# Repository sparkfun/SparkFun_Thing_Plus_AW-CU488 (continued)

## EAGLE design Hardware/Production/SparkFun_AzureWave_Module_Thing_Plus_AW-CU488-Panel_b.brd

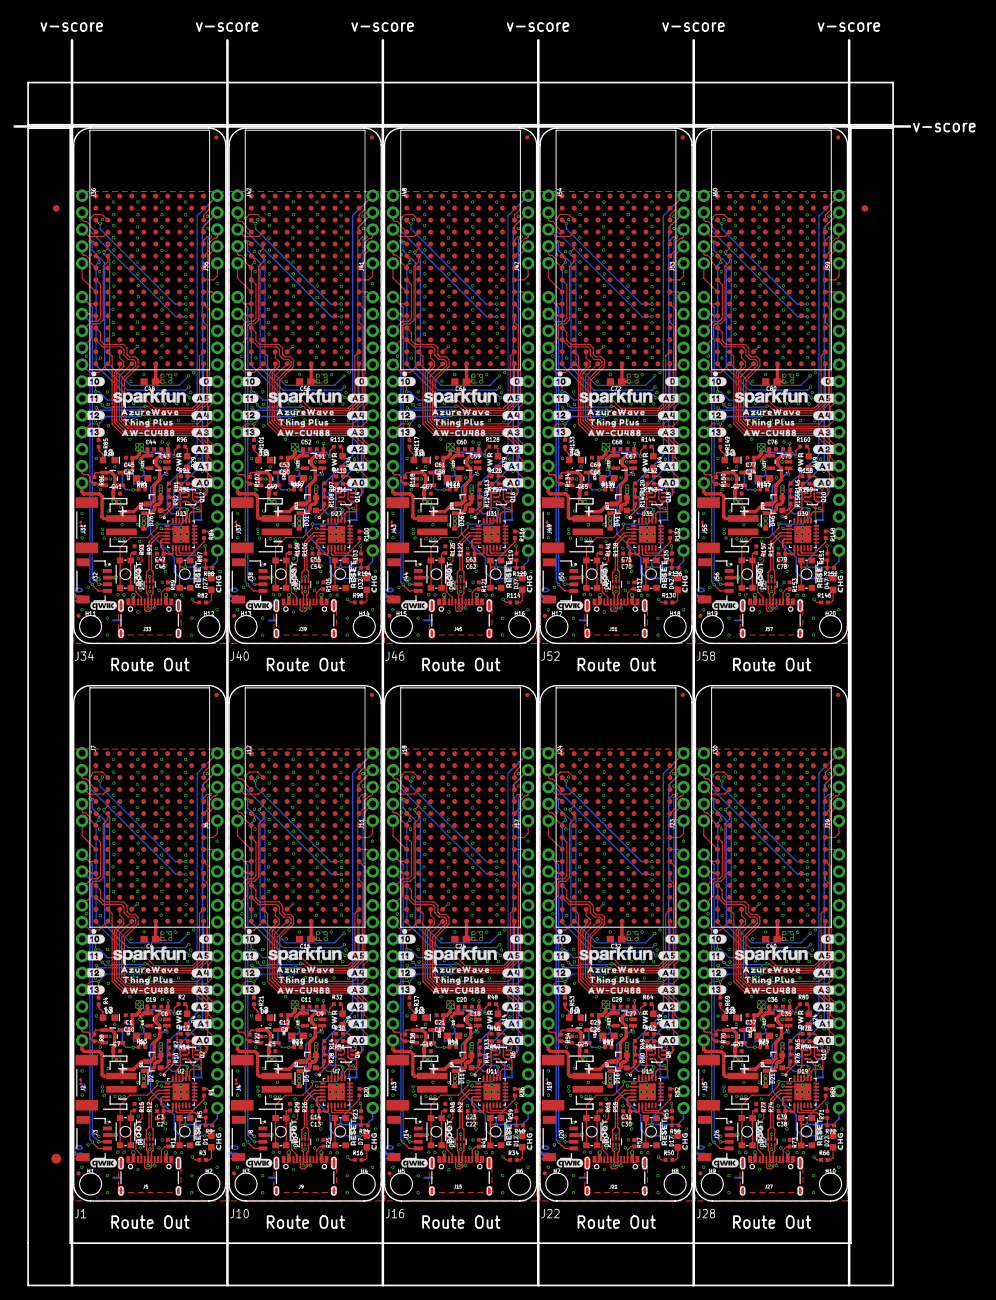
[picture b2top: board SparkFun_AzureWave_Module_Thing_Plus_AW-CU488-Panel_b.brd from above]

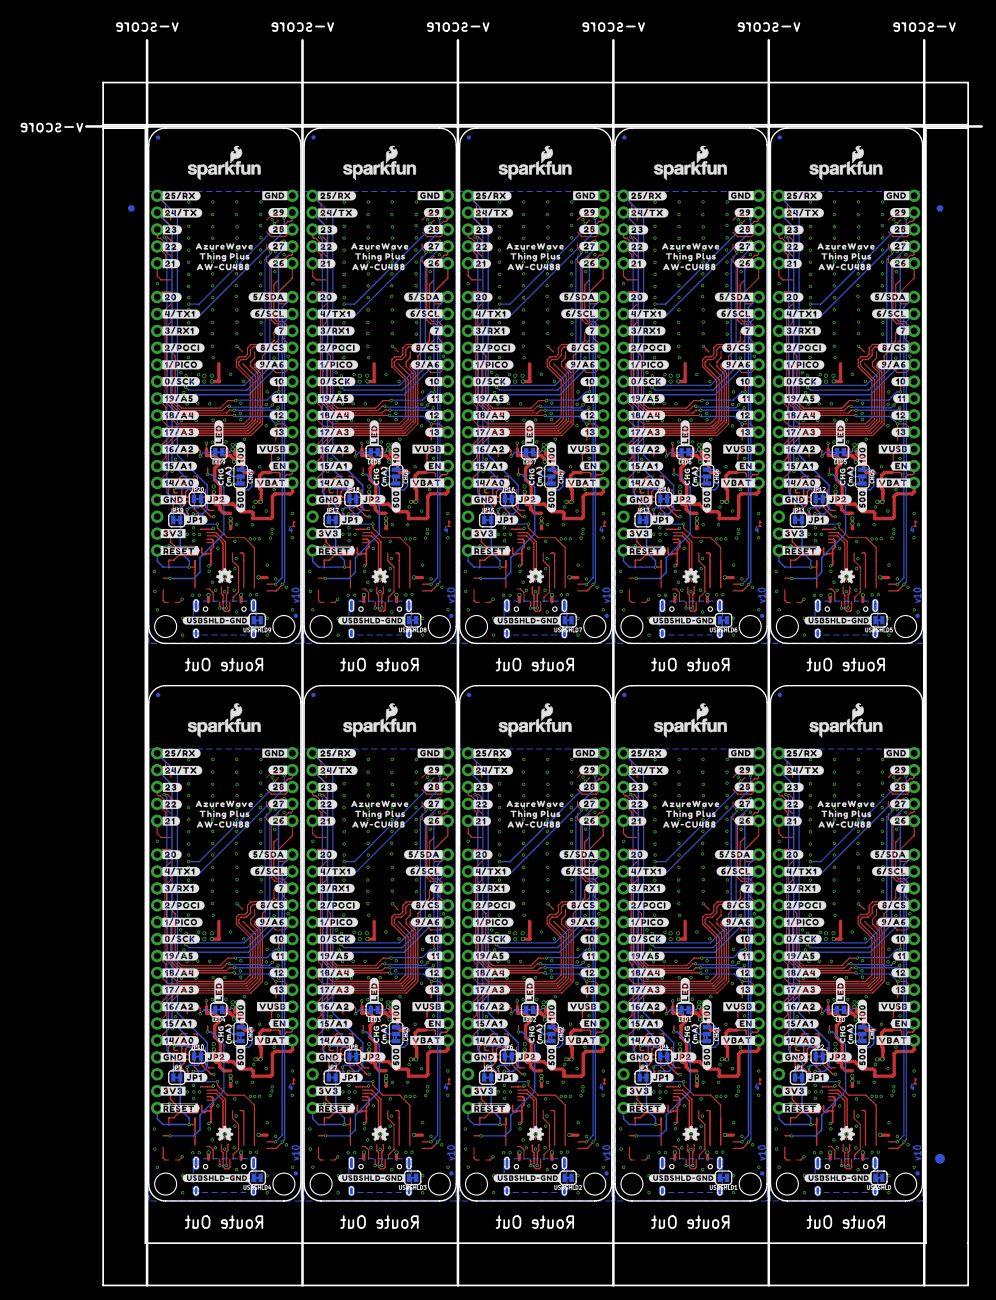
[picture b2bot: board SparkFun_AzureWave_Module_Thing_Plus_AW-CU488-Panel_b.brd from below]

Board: 4 copper layers, 134.6 x 187.2 mm, 1276 parts (573 on the bottom side), 620 nets.

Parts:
C1, C12, C21, C29, C37, C45, C53, C61, C69, C77: 10uF; 0402-TIGHT
C2, C13, C22, C30, C38, C46, C54, C62, C70, C78: 0.1uF; 0402-TIGHT
C3, C6, C9, C11, C14, C18, C19, C20, C23, C27, C28, C31, C35, C36, C39, C43, C44, C47, C51, C52, C55, C59, C60, C63, C67, C68, C71, C75, C76, C79: 4.7uF; 0402-TIGHT
C4, C15, C24, C32, C40, C48, C56, C64, C72, C80: 10uF; 0603
C5, C7, C8, C10, C16, C17, C25, C26, C33, C34, C41, C42, C49, C50, C57, C58, C65, C66, C73, C74: 1.0uF; 0402-TIGHT
CHG, CHG1, CHG2, CHG3, CHG4, CHG5, CHG6, CHG7, CHG8, CHG9: SMT-JUMPER_3_1-NC_TRACE_SILK
D1, D7, D12, D17, D22, D27, D32, D37, D42, D47: Yellow; LED-0603
D2, D5, D11, D16, D21, D26, D31, D36, D41, D46: 1A/23V/620mV; SOD-323
D3, D8, D13, D18, D23, D28, D33, D38, D43, D48: BLUE; LED-0603
D4, D9, D14, D19, D24, D29, D34, D39, D44, D49: RED; LED-0603
D6, D10, D15, D20, D25, D30, D35, D40, D45, D50: PRTR5V0U2F; SOT886
E$1, E$2, E$3, E$4: FIDUCIAL-1X2
E$5, E$6: FIDUCIAL-1.5X3
FD1, FD2, FD3, FD4, FD5, FD6, FD7, FD8, FD9, FD10, FD11, FD12, FD13, FD14, FD15, FD16, FD17, FD18, FD19, FD20, FD21, FD22, FD23, FD24, FD25, FD26, FD27, FD28, FD29, FD30, FD31, FD32, FD33, FD34, FD35, FD36, FD37, FD38, FD39, FD40: FIDUCIALUFIDUCIAL; FIDUCIAL-MICRO
H1, H2, H3, H4, H5, H6, H7, H8, H9, H10, H11, H12, H13, H14, H15, H16, H17, H18, H19, H20: STAND-OFF
J1, J10, J16, J22, J28, J34, J40, J46, J52, J58: THING_PLUS
J2, J4, J13, J19, J25, J31, J37, J43, J49, J55: LiPo; JST-2-SMD
J3, J8, J14, J20, J26, J32, J38, J44, J50, J56: QWIIC_RA; JST04_1MM_RA
J5, J9, J15, J21, J27, J33, J39, J45, J51, J57: USB-C; USB-C-16P-4LAYER-ISOLATED
J6, J7, J11, J12, J17, J18, J23, J24, J29, J30, J35, J36, J41, J42, J47, J48, J53, J54, J59, J60: 1X05_NO_SILK
JP1, JP2, JP3, JP4, JP5, JP6, JP7, JP8, JP9, JP10, JP11, JP12, JP13, JP14, JP15, JP16, JP17, JP18, JP19, JP20: SMT-JUMPER_2_NC_TRACE_SILK
LED, LED1, LED2, LED3, LED4, LED5, LED6, LED7, LED8, LED9: SMT-JUMPER_2_NC_TRACE_SILK
LOGO1, LOGO9, LOGO14, LOGO19, LOGO24, LOGO29, LOGO34, LOGO39, LOGO44, LOGO49: SFE_LOGO_NAME.1_INCH; SFE_LOGO_NAME_.1
LOGO2, LOGO5, LOGO11, LOGO16, LOGO21, LOGO26, LOGO31, LOGO36, LOGO41, LOGO46: OSHW-LOGOMINI; OSHW-LOGO-MINI
LOGO3, LOGO10, LOGO15, LOGO20, LOGO25, LOGO30, LOGO35, LOGO40, LOGO45, LOGO50: SFE_LOGO_NAME_FLAME.1_INCH; SFE_LOGO_NAME_FLAME_.1
LOGO4, LOGO7, LOGO12, LOGO17, LOGO22, LOGO27, LOGO32, LOGO37, LOGO42, LOGO47: FOUR_LAYER_WARNING
LOGO6, LOGO8, LOGO13, LOGO18, LOGO23, LOGO28, LOGO33, LOGO38, LOGO43, LOGO48: QWIIC_LOGO_4MM; QWIIC_4MM
Q1, Q3, Q5, Q7, Q9, Q11, Q13, Q15, Q17, Q19: 3.1A/30V/105mΩ; SOT23-3
Q2, Q4, Q6, Q8, Q10, Q12, Q14, Q16, Q18, Q20: MBT3904DW1T1; SC70-6
R1, R7, R13, R14, R17, R18, R20, R27, R30, R31, R33, R36, R43, R46, R47, R49, R52, R59, R62, R63, R65, R68, R75, R78, R79, R81, R84, R91, R94, R95, R97, R100, R107, R110, R111, R113, R116, R123, R126, R127, R129, R132, R139, R142, R143, R145, R148, R155, R158, R159: 10k; 0402-TIGHT
R2, R15, R29, R32, R45, R48, R61, R64, R77, R80, R93, R96, R109, R112, R125, R128, R141, R144, R157, R160: 1k; 0402-TIGHT
R3, R4, R16, R21, R34, R37, R50, R53, R66, R69, R82, R85, R98, R101, R114, R117, R130, R133, R146, R149: 4.7k; 0402-TIGHT
R5, R23, R39, R55, R71, R87, R103, R119, R135, R151: 22k; 0402-TIGHT
R6, R19, R35, R51, R67, R83, R99, R115, R131, R147: 2.0k; 0603
R8, R22, R38, R54, R70, R86, R102, R118, R134, R150: 100k; 0402-TIGHT
R9, R24, R40, R56, R72, R88, R104, R120, R136, R152: 33k; 0402-TIGHT
R10, R28, R44, R60, R76, R92, R108, R124, R140, R156: 100; 0402-TIGHT
R11, R12, R25, R26, R41, R42, R57, R58, R73, R74, R89, R90, R105, R106, R121, R122, R137, R138, R153, R154: 5.1k; 0402-TIGHT
S1, S3, S5, S7, S9, S11, S13, S15, S17, S19: SW1/RESET; TACTILE_SWITCH_SMD_4.6X2.8MM
S2, S4, S6, S8, S10, S12, S14, S16, S18, S20: SW2/BOOT; TACTILE_SWITCH_SMD_4.6X2.8MM
U1, U8, U12, U16, U20, U24, U28, U32, U36, U40: AW-CU488; LGA150_AW-CU488
U2, U7, U11, U15, U19, U23, U27, U31, U35, U39: CP210X; QFN24
U3, U6, U10, U14, U18, U22, U26, U30, U34, U38: XC6222B331MR-G; SOT23-5
U4, U5, U9, U13, U17, U21, U25, U29, U33, U37: MCP73831; SOT23-5
U$1, U$129, U$197, U$265, U$333, U$401, U$469, U$537, U$605, U$673: #10#30
U$2, U$38, U$152, U$220, U$288, U$356, U$424, U$492, U$560, U$628: BOOT0
U$3, U$17, U$31, U$78, U$138, U$146, U$206, U$214, U$274, U$282, U$342, U$350, U$410, U$418, U$478, U$486, U$546, U$554, U$614, U$622: CHG0
U$4, U$35, U$149, U$217, U$285, U$353, U$421, U$489, U$557, U$625: #500#0
U$5, U$130, U$198, U$266, U$334, U$402, U$470, U$538, U$606, U$674: #11#30
U$6, U$8, U$39, U$40, U$153, U$154, U$221, U$222, U$289, U$290, U$357, U$358, U$425, U$426, U$493, U$494, U$561, U$562, U$629, U$630: AZUREWAVE0
U$7, U$133, U$201, U$269, U$337, U$405, U$473, U$541, U$609, U$677: 1330
U$9, U$27, U$37, U$44, U$151, U$155, U$219, U$223, U$287, U$291, U$355, U$359, U$423, U$427, U$491, U$495, U$559, U$563, U$627, U$631: AW#CU488_0
U$10, U$36, U$47, U$62, U$150, U$156, U$218, U$224, U$286, U$292, U$354, U$360, U$422, U$428, U$490, U$496, U$558, U$564, U$626, U$632: THING_PLUS_0
U$11, U$33, U$147, U$215, U$283, U$351, U$419, U$487, U$555, U$623: MA0
U$12, U$131, U$199, U$267, U$335, U$403, U$471, U$539, U$607, U$675: #12#30
U$13, U$59, U$137, U$205, U$273, U$341, U$409, U$477, U$545, U$613: ORDERING_INSTRUCTIONS
U$14, U$132, U$200, U$268, U$336, U$404, U$472, U$540, U$608, U$676: #13#30
U$15, U$135, U$203, U$271, U$339, U$407, U$475, U$543, U$611, U$679: #JP1#1
U$16, U$134, U$202, U$270, U$338, U$406, U$474, U$542, U$610, U$678: #0#1
U$18, U$65, U$162, U$230, U$298, U$366, U$434, U$502, U$570, U$638: #A0#30
U$19, U$136, U$204, U$272, U$340, U$408, U$476, U$544, U$612, U$680: #JP2#4
U$20, U$66, U$163, U$231, U$299, U$367, U$435, U$503, U$571, U$639: #USBSHLD#GND#3
U$21, U$79, U$139, U$207, U$275, U$343, U$411, U$479, U$547, U$615: RESET0
U$22, U$41, U$140, U$208, U$276, U$344, U$412, U$480, U$548, U$616: #VUSB#0
U$23, U$96, U$164, U$232, U$300, U$368, U$436, U$504, U$572, U$640: PWR0
U$24, U$42, U$141, U$209, U$277, U$345, U$413, U$481, U$549, U$617: #VBAT#0
U$25, U$43, U$142, U$210, U$278, U$346, U$414, U$482, U$550, U$618: #EN#0
U$26, U$32, U$86, U$119, U$143, U$187, U$211, U$255, U$279, U$323, U$347, U$391, U$415, U$459, U$483, U$527, U$551, U$595, U$619, U$663: #GND#0
U$28, U$45, U$144, U$212, U$280, U$348, U$416, U$484, U$552, U$620: #3V3#0
U$29, U$97, U$165, U$233, U$301, U$369, U$437, U$505, U$573, U$641: #LED#0
U$30, U$46, U$145, U$213, U$281, U$349, U$417, U$485, U$553, U$621: ##RESET##0
U$34, U$60, U$148, U$216, U$284, U$352, U$420, U$488, U$556, U$624: #100#0
U$48, U$107, U$175, U$243, U$311, U$379, U$447, U$515, U$583, U$651: #4#TX1#14
U$49, U$108, U$176, U$244, U$312, U$380, U$448, U$516, U$584, U$652: #3#RX1#14
U$50, U$109, U$177, U$245, U$313, U$381, U$449, U$517, U$585, U$653: #2#POCI#14
U$51, U$53, U$157, U$225, U$293, U$361, U$429, U$497, U$565, U$633: #A1#6
U$52, U$54, U$158, U$226, U$294, U$362, U$430, U$498, U$566, U$634: #A2#6
U$55, U$58, U$159, U$227, U$295, U$363, U$431, U$499, U$567, U$635: #A3#6
U$56, U$61, U$160, U$228, U$296, U$364, U$432, U$500, U$568, U$636: #A4#6
U$57, U$63, U$161, U$229, U$297, U$365, U$433, U$501, U$569, U$637: #A5#6
U$64, U$110, U$178, U$246, U$314, U$382, U$450, U$518, U$586, U$654: #1#PICO#14
U$67, U$98, U$166, U$234, U$302, U$370, U$438, U$506, U$574, U$642: #13#14
U$68, U$99, U$167, U$235, U$303, U$371, U$439, U$507, U$575, U$643: #12#14
U$69, U$100, U$168, U$236, U$304, U$372, U$440, U$508, U$576, U$644: #11#14
U$70, U$101, U$169, U$237, U$305, U$373, U$441, U$509, U$577, U$645: #10#14
U$71, U$102, U$170, U$238, U$306, U$374, U$442, U$510, U$578, U$646: #9#A6#14
U$72, U$103, U$171, U$239, U$307, U$375, U$443, U$511, U$579, U$647: #8#CS#14
U$73, U$104, U$172, U$240, U$308, U$376, U$444, U$512, U$580, U$648: #7#14
U$74, U$105, U$173, U$241, U$309, U$377, U$445, U$513, U$581, U$649: #6#SCL#14
U$75, U$106, U$174, U$242, U$310, U$378, U$446, U$514, U$582, U$650: #5#SDA#14
U$76, U$111, U$179, U$247, U$315, U$383, U$451, U$519, U$587, U$655: #0#SCK#14
U$77, U$112, U$180, U$248, U$316, U$384, U$452, U$520, U$588, U$656: #14#A0#15
U$80, U$113, U$181, U$249, U$317, U$385, U$453, U$521, U$589, U$657: #15#A1#15
U$81, U$114, U$182, U$250, U$318, U$386, U$454, U$522, U$590, U$658: #16#A2#16
U$82, U$115, U$183, U$251, U$319, U$387, U$455, U$523, U$591, U$659: #17#A3#17
U$83, U$116, U$184, U$252, U$320, U$388, U$456, U$524, U$592, U$660: #18#A4#18
U$84, U$117, U$185, U$253, U$321, U$389, U$457, U$525, U$593, U$661: #19#A5#19
U$85, U$118, U$186, U$254, U$322, U$390, U$458, U$526, U$594, U$662: #20#20
U$87, U$120, U$188, U$256, U$324, U$392, U$460, U$528, U$596, U$664: #21#21
U$88, U$121, U$189, U$257, U$325, U$393, U$461, U$529, U$597, U$665: #22#22
U$89, U$122, U$190, U$258, U$326, U$394, U$462, U$530, U$598, U$666: #23#23
U$90, U$123, U$191, U$259, U$327, U$395, U$463, U$531, U$599, U$667: #24#TX#24
U$91, U$124, U$192, U$260, U$328, U$396, U$464, U$532, U$600, U$668: #25#RX#25
U$92, U$125, U$193, U$261, U$329, U$397, U$465, U$533, U$601, U$669: #26#26
U$93, U$126, U$194, U$262, U$330, U$398, U$466, U$534, U$602, U$670: #27#27
U$94, U$127, U$195, U$263, U$331, U$399, U$467, U$535, U$603, U$671: #28#28
U$95, U$128, U$196, U$264, U$332, U$400, U$468, U$536, U$604, U$672: #29#29
USBSHLD, USBSHLD1, USBSHLD2, USBSHLD3, USBSHLD4, USBSHLD5, USBSHLD6, USBSHLD7, USBSHLD8, USBSHLD9: SMT-JUMPER_2_NC_TRACE_SILK

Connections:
3.3V: C1.1, C2.1, C3.1, C4.1, C10.1, J1.27, J3.2, LED.1, R1.1, U1.F1, U2.5, U2.6, U2.7, U3.5
3.3V1: C8.1, C12.1, C13.1, C14.1, C15.1, J8.2, J10.27, LED1.1, R20.1, U6.5, U7.5, U7.6, U7.7, U8.F1
3.3V2: C17.1, C21.1, C22.1, C23.1, C24.1, J14.2, J16.27, LED2.1, R36.1, U10.5, U11.5, U11.6, U11.7, U12.F1
3.3V3: C26.1, C29.1, C30.1, C31.1, C32.1, J20.2, J22.27, LED3.1, R52.1, U14.5, U15.5, U15.6, U15.7, U16.F1
3.3V4: C34.1, C37.1, C38.1, C39.1, C40.1, J26.2, J28.27, LED4.1, R68.1, U18.5, U19.5, U19.6, U19.7, U20.F1
3.3V5: C42.1, C45.1, C46.1, C47.1, C48.1, J32.2, J34.27, LED5.1, R84.1, U22.5, U23.5, U23.6, U23.7, U24.F1
3.3V6: C50.1, C53.1, C54.1, C55.1, C56.1, J38.2, J40.27, LED6.1, R100.1, U26.5, U27.5, U27.6, U27.7, U28.F1
3.3V7: C58.1, C61.1, C62.1, C63.1, C64.1, J44.2, J46.27, LED7.1, R116.1, U30.5, U31.5, U31.6, U31.7, U32.F1
3.3V8: C66.1, C69.1, C70.1, C71.1, C72.1, J50.2, J52.27, LED8.1, R132.1, U34.5, U35.5, U35.6, U35.7, U36.F1
3.3V9: C74.1, C77.1, C78.1, C79.1, C80.1, J56.2, J58.27, LED9.1, R148.1, U38.5, U39.5, U39.6, U39.7, U40.F1
CC1: J5.A5, R12.2
CC2: J5.B5, R11.2
CC3: J9.B5, R25.2
CC4: J9.A5, R26.2
CC5: J15.B5, R41.2
CC6: J15.A5, R42.2
CC7: J21.B5, R57.2
CC8: J21.A5, R58.2
CC9: J27.B5, R73.2
CC10: J27.A5, R74.2
CC11: J33.B5, R89.2
CC12: J33.A5, R90.2
CC13: J39.B5, R105.2
CC14: J39.A5, R106.2
CC15: J45.B5, R121.2
CC16: J45.A5, R122.2
CC17: J51.B5, R137.2
CC18: J51.A5, R138.2
CC19: J57.B5, R153.2
CC20: J57.A5, R154.2
CHG: D1.C, U4.1
CHG1: D7.C, U5.1
CHG2: D12.C, U9.1
CHG3: D17.C, U13.1
CHG4: D22.C, U17.1
CHG5: D27.C, U21.1
CHG6: D32.C, U25.1
CHG7: D37.C, U29.1
CHG8: D42.C, U33.1
CHG9: D47.C, U37.1
CHIP_EN: J1.28, JP1.2, S1.1, S1.2, U1.K11
CHIP_EN1: J10.28, JP3.2, S3.1, S3.2, U8.K11
CHIP_EN2: J16.28, JP5.2, S5.1, S5.2, U12.K11
CHIP_EN3: J22.28, JP7.2, S7.1, S7.2, U16.K11
CHIP_EN4: J28.28, JP9.2, S9.1, S9.2, U20.K11
CHIP_EN5: J34.28, JP11.2, S11.1, S11.2, U24.K11
CHIP_EN6: J40.28, JP13.2, S13.1, S13.2, U28.K11
CHIP_EN7: J46.28, JP15.2, S15.1, S15.2, U32.K11
CHIP_EN8: J52.28, JP17.2, S17.1, S17.2, U36.K11
CHIP_EN9: J58.28, JP19.2, S19.1, S19.2, U40.K11
DTR: Q2.1, R17.1, U2.23
DTR1: Q4.1, R30.1, U7.23
DTR2: Q6.1, R46.1, U11.23
DTR3: Q8.1, R62.1, U15.23
DTR4: Q10.1, R78.1, U19.23
DTR5: Q12.1, R94.1, U23.23
DTR6: Q14.1, R110.1, U27.23
DTR7: Q16.1, R126.1, U31.23
DTR8: Q18.1, R142.1, U35.23
DTR9: Q20.1, R158.1, U39.23
EN: J1.11, R8.2, U3.3
EN1: J10.11, R22.2, U6.3
EN2: J16.11, R38.2, U10.3
EN3: J22.11, R54.2, U14.3
EN4: J28.11, R70.2, U18.3
EN5: J34.11, R86.2, U22.3
EN6: J40.11, R102.2, U26.3
EN7: J46.11, R118.2, U30.3
EN8: J52.11, R134.2, U34.3
EN9: J58.11, R150.2, U38.3
GND: C1.2, C2.2, C3.2, C4.2, C6.2, C7.2, C10.2, C19.2, D3.C, D4.C, D6.2, J1.25, J2.1, J3.1, J5.GND, J5.GND2, J7.1, R6.1, R7.1, R9.1, R11.1, R12.1, R13.2, R15.1, S1.3, S1.4, U1.A1, U1.A2, U1.A14, U1.A15, U1.B14, U1.B15, U1.C3, U1.C4, U1.C5, U1.C6, U1.C7, U1.C8, U1.C9, U1.C10, U1.C11, U1.C12, U1.C13, U1.C14, U1.C15, U1.D3, U1.D4, U1.D5, U1.D6, U1.D7, U1.D8, U1.D9, U1.D10, U1.D11, U1.D12, U1.D13, U1.D14, U1.D15, U1.E1, U1.E2, U1.E3, U1.E4, U1.E5, U1.E6, U1.E7, U1.E8, U1.E9, U1.E10, U1.E11, U1.E12, U1.E13, U1.E14, U1.E15, U1.F2, U1.F3, U1.F4, U1.F5, U1.F6, U1.F7, U1.F8, U1.F9, U1.F10, U1.F11, U1.F12, U1.F13, U1.F14, U1.F15, U1.G1, U1.G2, U1.G3, U1.G4, U1.G5, U1.G6, U1.G7, U1.G8, U1.G9, U1.G10, U1.G11, U1.G12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
GND1: C5.2, C8.2, C9.2, C11.2, C12.2, C13.2, C14.2, C15.2, D8.C, D9.C, D10.2, J4.1, J8.1, J9.GND, J9.GND2, J10.25, J12.1, R14.1, R19.1, R24.1, R25.1, R26.1, R27.2, R29.1, S3.3, S3.4, U5.2, U6.2, U7.2, U7.PAD, U8.A1, U8.A2, U8.A14, U8.A15, U8.B14, U8.B15, U8.C3, U8.C4, U8.C5, U8.C6, U8.C7, U8.C8, U8.C9, U8.C10, U8.C11, U8.C12, U8.C13, U8.C14, U8.C15, U8.D3, U8.D4, U8.D5, U8.D6, U8.D7, U8.D8, U8.D9, U8.D10, U8.D11, U8.D12, U8.D13, U8.D14, U8.D15, U8.E1, U8.E2, U8.E3, U8.E4, U8.E5, U8.E6, U8.E7, U8.E8, U8.E9, U8.E10, U8.E11, U8.E12, U8.E13, U8.E14, U8.E15, U8.F2, U8.F3, U8.F4, U8.F5, U8.F6, U8.F7, U8.F8, U8.F9, U8.F10, U8.F11, U8.F12, U8.F13, U8.F14, U8.F15, U8.G1, U8.G2, U8.G3, U8.G4, U8.G5, U8.G6, U8.G7, U8.G8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
GND2: C16.2, C17.2, C18.2, C20.2, C21.2, C22.2, C23.2, C24.2, D13.C, D14.C, D15.2, J13.1, J14.1, J15.GND, J15.GND2, J16.25, J18.1, R33.1, R35.1, R40.1, R41.1, R42.1, R43.2, R45.1, S5.3, S5.4, U9.2, U10.2, U11.2, U11.PAD, U12.A1, U12.A2, U12.A14, U12.A15, U12.B14, U12.B15, U12.C3, U12.C4, U12.C5, U12.C6, U12.C7, U12.C8, U12.C9, U12.C10, U12.C11, U12.C12, U12.C13, U12.C14, U12.C15, U12.D3, U12.D4, U12.D5, U12.D6, U12.D7, U12.D8, U12.D9, U12.D10, U12.D11, U12.D12, U12.D13, U12.D14, U12.D15, U12.E1, U12.E2, U12.E3, U12.E4, U12.E5, U12.E6, U12.E7, U12.E8, U12.E9, U12.E10, U12.E11, U12.E12, U12.E13, U12.E14, U12.E15, U12.F2, U12.F3, U12.F4, U12.F5, U12.F6, U12.F7, U12.F8, U12.F9, U12.F10, U12.F11, U12.F12, U12.F13, U12.F14, U12.F15, U12.G1, U12.G2, U12.G3, U12.G4, U12.G5, U12.G6, U12.G7, U12.G8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
GND3: C25.2, C26.2, C27.2, C28.2, C29.2, C30.2, C31.2, C32.2, D18.C, D19.C, D20.2, J19.1, J20.1, J21.GND, J21.GND2, J22.25, J24.1, R49.1, R51.1, R56.1, R57.1, R58.1, R59.2, R61.1, S7.3, S7.4, U13.2, U14.2, U15.2, U15.PAD, U16.A1, U16.A2, U16.A14, U16.A15, U16.B14, U16.B15, U16.C3, U16.C4, U16.C5, U16.C6, U16.C7, U16.C8, U16.C9, U16.C10, U16.C11, U16.C12, U16.C13, U16.C14, U16.C15, U16.D3, U16.D4, U16.D5, U16.D6, U16.D7, U16.D8, U16.D9, U16.D10, U16.D11, U16.D12, U16.D13, U16.D14, U16.D15, U16.E1, U16.E2, U16.E3, U16.E4, U16.E5, U16.E6, U16.E7, U16.E8, U16.E9, U16.E10, U16.E11, U16.E12, U16.E13, U16.E14, U16.E15, U16.F2, U16.F3, U16.F4, U16.F5, U16.F6, U16.F7, U16.F8, U16.F9, U16.F10, U16.F11, U16.F12, U16.F13, U16.F14, U16.F15, U16.G1, U16.G2, U16.G3, U16.G4, U16.G5, U16.G6, U16.G7, U16.G8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
GND4: C33.2, C34.2, C35.2, C36.2, C37.2, C38.2, C39.2, C40.2, D23.C, D24.C, D25.2, J25.1, J26.1, J27.GND, J27.GND2, J28.25, J30.1, R65.1, R67.1, R72.1, R73.1, R74.1, R75.2, R77.1, S9.3, S9.4, U17.2, U18.2, U19.2, U19.PAD, U20.A1, U20.A2, U20.A14, U20.A15, U20.B14, U20.B15, U20.C3, U20.C4, U20.C5, U20.C6, U20.C7, U20.C8, U20.C9, U20.C10, U20.C11, U20.C12, U20.C13, U20.C14, U20.C15, U20.D3, U20.D4, U20.D5, U20.D6, U20.D7, U20.D8, U20.D9, U20.D10, U20.D11, U20.D12, U20.D13, U20.D14, U20.D15, U20.E1, U20.E2, U20.E3, U20.E4, U20.E5, U20.E6, U20.E7, U20.E8, U20.E9, U20.E10, U20.E11, U20.E12, U20.E13, U20.E14, U20.E15, U20.F2, U20.F3, U20.F4, U20.F5, U20.F6, U20.F7, U20.F8, U20.F9, U20.F10, U20.F11, U20.F12, U20.F13, U20.F14, U20.F15, U20.G1, U20.G2, U20.G3, U20.G4, U20.G5, U20.G6, U20.G7, U20.G8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
GND5: C41.2, C42.2, C43.2, C44.2, C45.2, C46.2, C47.2, C48.2, D28.C, D29.C, D30.2, J31.1, J32.1, J33.GND, J33.GND2, J34.25, J36.1, R81.1, R83.1, R88.1, R89.1, R90.1, R91.2, R93.1, S11.3, S11.4, U21.2, U22.2, U23.2, U23.PAD, U24.A1, U24.A2, U24.A14, U24.A15, U24.B14, U24.B15, U24.C3, U24.C4, U24.C5, U24.C6, U24.C7, U24.C8, U24.C9, U24.C10, U24.C11, U24.C12, U24.C13, U24.C14, U24.C15, U24.D3, U24.D4, U24.D5, U24.D6, U24.D7, U24.D8, U24.D9, U24.D10, U24.D11, U24.D12, U24.D13, U24.D14, U24.D15, U24.E1, U24.E2, U24.E3, U24.E4, U24.E5, U24.E6, U24.E7, U24.E8, U24.E9, U24.E10, U24.E11, U24.E12, U24.E13, U24.E14, U24.E15, U24.F2, U24.F3, U24.F4, U24.F5, U24.F6, U24.F7, U24.F8, U24.F9, U24.F10, U24.F11, U24.F12, U24.F13, U24.F14, U24.F15, U24.G1, U24.G2, U24.G3, U24.G4, U24.G5, U24.G6, U24.G7, U24.G8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
GND6: C49.2, C50.2, C51.2, C52.2, C53.2, C54.2, C55.2, C56.2, D33.C, D34.C, D35.2, J37.1, J38.1, J39.GND, J39.GND2, J40.25, J42.1, R97.1, R99.1, R104.1, R105.1, R106.1, R107.2, R109.1, S13.3, S13.4, U25.2, U26.2, U27.2, U27.PAD, U28.A1, U28.A2, U28.A14, U28.A15, U28.B14, U28.B15, U28.C3, U28.C4, U28.C5, U28.C6, U28.C7, U28.C8, U28.C9, U28.C10, U28.C11, U28.C12, U28.C13, U28.C14, U28.C15, U28.D3, U28.D4, U28.D5, U28.D6, U28.D7, U28.D8, U28.D9, U28.D10, U28.D11, U28.D12, U28.D13, U28.D14, U28.D15, U28.E1, U28.E2, U28.E3, U28.E4, U28.E5, U28.E6, U28.E7, U28.E8, U28.E9, U28.E10, U28.E11, U28.E12, U28.E13, U28.E14, U28.E15, U28.F2, U28.F3, U28.F4, U28.F5, U28.F6, U28.F7, U28.F8, U28.F9, U28.F10, U28.F11, U28.F12, U28.F13, U28.F14, U28.F15, U28.G1, U28.G2, U28.G3, U28.G4, U28.G5, U28.G6, U28.G7, U28.G8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
GND7: C57.2, C58.2, C59.2, C60.2, C61.2, C62.2, C63.2, C64.2, D38.C, D39.C, D40.2, J43.1, J44.1, J45.GND, J45.GND2, J46.25, J48.1, R113.1, R115.1, R120.1, R121.1, R122.1, R123.2, R125.1, S15.3, S15.4, U29.2, U30.2, U31.2, U31.PAD, U32.A1, U32.A2, U32.A14, U32.A15, U32.B14, U32.B15, U32.C3, U32.C4, U32.C5, U32.C6, U32.C7, U32.C8, U32.C9, U32.C10, U32.C11, U32.C12, U32.C13, U32.C14, U32.C15, U32.D3, U32.D4, U32.D5, U32.D6, U32.D7, U32.D8, U32.D9, U32.D10, U32.D11, U32.D12, U32.D13, U32.D14, U32.D15, U32.E1, U32.E2, U32.E3, U32.E4, U32.E5, U32.E6, U32.E7, U32.E8, U32.E9, U32.E10, U32.E11, U32.E12, U32.E13, U32.E14, U32.E15, U32.F2, U32.F3, U32.F4, U32.F5, U32.F6, U32.F7, U32.F8, U32.F9, U32.F10, U32.F11, U32.F12, U32.F13, U32.F14, U32.F15, U32.G1, U32.G2, U32.G3, U32.G4, U32.G5, U32.G6, U32.G7, U32.G8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
GND8: C65.2, C66.2, C67.2, C68.2, C69.2, C70.2, C71.2, C72.2, D43.C, D44.C, D45.2, J49.1, J50.1, J51.GND, J51.GND2, J52.25, J54.1, R129.1, R131.1, R136.1, R137.1, R138.1, R139.2, R141.1, S17.3, S17.4, U33.2, U34.2, U35.2, U35.PAD, U36.A1, U36.A2, U36.A14, U36.A15, U36.B14, U36.B15, U36.C3, U36.C4, U36.C5, U36.C6, U36.C7, U36.C8, U36.C9, U36.C10, U36.C11, U36.C12, U36.C13, U36.C14, U36.C15, U36.D3, U36.D4, U36.D5, U36.D6, U36.D7, U36.D8, U36.D9, U36.D10, U36.D11, U36.D12, U36.D13, U36.D14, U36.D15, U36.E1, U36.E2, U36.E3, U36.E4, U36.E5, U36.E6, U36.E7, U36.E8, U36.E9, U36.E10, U36.E11, U36.E12, U36.E13, U36.E14, U36.E15, U36.F2, U36.F3, U36.F4, U36.F5, U36.F6, U36.F7, U36.F8, U36.F9, U36.F10, U36.F11, U36.F12, U36.F13, U36.F14, U36.F15, U36.G1, U36.G2, U36.G3, U36.G4, U36.G5, U36.G6, U36.G7, U36.G8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
GND9: C73.2, C74.2, C75.2, C76.2, C77.2, C78.2, C79.2, C80.2, D48.C, D49.C, D50.2, J55.1, J56.1, J57.GND, J57.GND2, J58.25, J60.1, R145.1, R147.1, R152.1, R153.1, R154.1, R155.2, R157.1, S19.3, S19.4, U37.2, U38.2, U39.2, U39.PAD, U40.A1, U40.A2, U40.A14, U40.A15, U40.B14, U40.B15, U40.C3, U40.C4, U40.C5, U40.C6, U40.C7, U40.C8, U40.C9, U40.C10, U40.C11, U40.C12, U40.C13, U40.C14, U40.C15, U40.D3, U40.D4, U40.D5, U40.D6, U40.D7, U40.D8, U40.D9, U40.D10, U40.D11, U40.D12, U40.D13, U40.D14, U40.D15, U40.E1, U40.E2, U40.E3, U40.E4, U40.E5, U40.E6, U40.E7, U40.E8, U40.E9, U40.E10, U40.E11, U40.E12, U40.E13, U40.E14, U40.E15, U40.F2, U40.F3, U40.F4, U40.F5, U40.F6, U40.F7, U40.F8, U40.F9, U40.F10, U40.F11, U40.F12, U40.F13, U40.F14, U40.F15, U40.G1, U40.G2, U40.G3, U40.G4, U40.G5, U40.G6, U40.G7, U40.G8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
LP_UART_RXD: J1.15, U1.B13
LP_UART_RXD1: J10.15, U8.B13
LP_UART_RXD2: J16.15, U12.B13
LP_UART_RXD3: J22.15, U16.B13
LP_UART_RXD4: J28.15, U20.B13
LP_UART_RXD5: J34.15, U24.B13
LP_UART_RXD6: J40.15, U28.B13
LP_UART_RXD7: J46.15, U32.B13
LP_UART_RXD8: J52.15, U36.B13
LP_UART_RXD9: J58.15, U40.B13
LP_UART_TXD: J1.14, U1.A13
LP_UART_TXD1: J10.14, U8.A13
LP_UART_TXD2: J16.14, U12.A13
LP_UART_TXD3: J22.14, U16.A13
LP_UART_TXD4: J28.14, U20.A13
LP_UART_TXD5: J34.14, U24.A13
LP_UART_TXD6: J40.14, U28.A13
LP_UART_TXD7: J46.14, U32.A13
LP_UART_TXD8: J52.14, U36.A13
LP_UART_TXD9: J58.14, U40.A13
unnamed: R1.2, U2.9
unnamed: D3.A, R4.2
unnamed: Q2.5, R17.2
unnamed: R5.1, R9.2, U2.8
unnamed: Q2.2, R18.2
unnamed: JP1.1, Q2.3
unnamed: Q1.1, R10.2
unnamed: R15.2, S2.3, S2.4
unnamed: CHG.2, U4.5
unnamed: JP2.1, Q2.6
unnamed: CHG.1, R13.1
unnamed: LED.2, R2.1
unnamed: CHG.3, R6.2
unnamed: D4.A, R2.2
unnamed: D6.6, U2.3
unnamed: D6.1, J5.A6, J5.B6
unnamed: D1.A, R3.2
unnamed: D6.4, U2.4
unnamed: D6.3, J5.A7, J5.B7
unnamed: D7.A, R16.2
unnamed: R20.2, U7.9
unnamed: D8.A, R21.2
unnamed: R23.1, R24.2, U7.8
unnamed: CHG1.2, U5.5
unnamed: CHG1.1, R27.1
unnamed: CHG1.3, R19.2
unnamed: Q3.1, R28.2
unnamed: R29.2, S4.3, S4.4
unnamed: Q4.5, R30.2
unnamed: Q4.2, R31.2
unnamed: LED1.2, R32.1
unnamed: D9.A, R32.2
unnamed: D10.6, U7.3
unnamed: D10.1, J9.A6, J9.B6
unnamed: D10.4, U7.4
unnamed: D10.3, J9.A7, J9.B7
unnamed: JP3.1, Q4.3
unnamed: JP4.1, Q4.6
unnamed: D12.A, R34.2
unnamed: R36.2, U11.9
unnamed: D13.A, R37.2
unnamed: R39.1, R40.2, U11.8
unnamed: CHG2.2, U9.5
unnamed: CHG2.1, R43.1
unnamed: CHG2.3, R35.2
unnamed: Q5.1, R44.2
unnamed: R45.2, S6.3, S6.4
unnamed: Q6.5, R46.2
unnamed: Q6.2, R47.2
unnamed: LED2.2, R48.1
unnamed: D14.A, R48.2
unnamed: D15.6, U11.3
unnamed: D15.1, J15.A6, J15.B6
unnamed: D15.4, U11.4
unnamed: D15.3, J15.A7, J15.B7
unnamed: JP5.1, Q6.3
unnamed: JP6.1, Q6.6
unnamed: D17.A, R50.2
unnamed: R52.2, U15.9
unnamed: D18.A, R53.2
unnamed: R55.1, R56.2, U15.8
unnamed: CHG3.2, U13.5
unnamed: CHG3.1, R59.1
unnamed: CHG3.3, R51.2
unnamed: Q7.1, R60.2
unnamed: R61.2, S8.3, S8.4
unnamed: Q8.5, R62.2
unnamed: Q8.2, R63.2
unnamed: LED3.2, R64.1
unnamed: D19.A, R64.2
unnamed: D20.6, U15.3
unnamed: D20.1, J21.A6, J21.B6
unnamed: D20.4, U15.4
unnamed: D20.3, J21.A7, J21.B7
unnamed: JP7.1, Q8.3
unnamed: JP8.1, Q8.6
unnamed: D22.A, R66.2
unnamed: R68.2, U19.9
unnamed: D23.A, R69.2
unnamed: R71.1, R72.2, U19.8
unnamed: CHG4.2, U17.5
unnamed: CHG4.1, R75.1
unnamed: CHG4.3, R67.2
unnamed: Q9.1, R76.2
unnamed: R77.2, S10.3, S10.4
unnamed: Q10.5, R78.2
unnamed: Q10.2, R79.2
unnamed: LED4.2, R80.1
unnamed: D24.A, R80.2
unnamed: D25.6, U19.3
unnamed: D25.1, J27.A6, J27.B6
unnamed: D25.4, U19.4
unnamed: D25.3, J27.A7, J27.B7
unnamed: JP9.1, Q10.3
unnamed: JP10.1, Q10.6
unnamed: D27.A, R82.2
unnamed: R84.2, U23.9
unnamed: D28.A, R85.2
unnamed: R87.1, R88.2, U23.8
unnamed: CHG5.2, U21.5
unnamed: CHG5.1, R91.1
unnamed: CHG5.3, R83.2
unnamed: Q11.1, R92.2
unnamed: R93.2, S12.3, S12.4
unnamed: Q12.5, R94.2
unnamed: Q12.2, R95.2
unnamed: LED5.2, R96.1
unnamed: D29.A, R96.2
unnamed: D30.6, U23.3
unnamed: D30.1, J33.A6, J33.B6
unnamed: D30.4, U23.4
unnamed: D30.3, J33.A7, J33.B7
unnamed: JP11.1, Q12.3
unnamed: JP12.1, Q12.6
unnamed: D32.A, R98.2
unnamed: R100.2, U27.9
unnamed: D33.A, R101.2
unnamed: R103.1, R104.2, U27.8
unnamed: CHG6.2, U25.5
unnamed: CHG6.1, R107.1
unnamed: CHG6.3, R99.2
unnamed: Q13.1, R108.2
unnamed: R109.2, S14.3, S14.4
unnamed: Q14.5, R110.2
unnamed: Q14.2, R111.2
unnamed: LED6.2, R112.1
unnamed: D34.A, R112.2
unnamed: D35.6, U27.3
unnamed: D35.1, J39.A6, J39.B6
unnamed: D35.4, U27.4
unnamed: D35.3, J39.A7, J39.B7
unnamed: JP13.1, Q14.3
unnamed: JP14.1, Q14.6
unnamed: D37.A, R114.2
unnamed: R116.2, U31.9
unnamed: D38.A, R117.2
unnamed: R119.1, R120.2, U31.8
unnamed: CHG7.2, U29.5
unnamed: CHG7.1, R123.1
unnamed: CHG7.3, R115.2
unnamed: Q15.1, R124.2
unnamed: R125.2, S16.3, S16.4
unnamed: Q16.5, R126.2
unnamed: Q16.2, R127.2
unnamed: LED7.2, R128.1
unnamed: D39.A, R128.2
unnamed: D40.6, U31.3
unnamed: D40.1, J45.A6, J45.B6
unnamed: D40.4, U31.4
unnamed: D40.3, J45.A7, J45.B7
unnamed: JP15.1, Q16.3
unnamed: JP16.1, Q16.6
unnamed: D42.A, R130.2
unnamed: R132.2, U35.9
unnamed: D43.A, R133.2
unnamed: R135.1, R136.2, U35.8
unnamed: CHG8.2, U33.5
unnamed: CHG8.1, R139.1
unnamed: CHG8.3, R131.2
unnamed: Q17.1, R140.2
unnamed: R141.2, S18.3, S18.4
unnamed: Q18.5, R142.2
unnamed: Q18.2, R143.2
unnamed: LED8.2, R144.1
unnamed: D44.A, R144.2
unnamed: D45.6, U35.3
unnamed: D45.1, J51.A6, J51.B6
unnamed: D45.4, U35.4
unnamed: D45.3, J51.A7, J51.B7
unnamed: JP17.1, Q18.3
unnamed: JP18.1, Q18.6
unnamed: D47.A, R146.2
unnamed: R148.2, U39.9
unnamed: D48.A, R149.2
unnamed: R151.1, R152.2, U39.8
unnamed: CHG9.2, U37.5
unnamed: CHG9.1, R155.1
unnamed: CHG9.3, R147.2
unnamed: Q19.1, R156.2
unnamed: R157.2, S20.3, S20.4
unnamed: Q20.5, R158.2
unnamed: Q20.2, R159.2
unnamed: LED9.2, R160.1
unnamed: D49.A, R160.2
unnamed: D50.6, U39.3
unnamed: D50.1, J57.A6, J57.B6
unnamed: D50.4, U39.4
unnamed: D50.3, J57.A7, J57.B7
unnamed: JP19.1, Q20.3
unnamed: JP20.1, Q20.6
PA0: J6.1, U1.K8
PA1: J12.4, U8.A9
PA2: J6.3, U1.K10
PA3: J10.3, U8.A8
PA4: J6.2, U1.K9
PA5: J11.3, U8.K10
PA6: J11.1, U8.K8
PA7: J11.2, U8.K9
PA7/UART-LOG-TXD: J6.4, JP2.2, S2.1, S2.2, U1.K12, U2.20
PA7/UART-LOG-TXD1: J11.4, JP4.2, S4.1, S4.2, U7.20, U8.K12
PA7/UART-LOG-TXD2: J17.4, JP6.2, S6.1, S6.2, U11.20, U12.K12
PA7/UART-LOG-TXD3: J23.4, JP8.2, S8.1, S8.2, U15.20, U16.K12
PA7/UART-LOG-TXD4: J29.4, JP10.2, S10.1, S10.2, U19.20, U20.K12
PA7/UART-LOG-TXD5: J35.4, JP12.2, S12.1, S12.2, U23.20, U24.K12
PA7/UART-LOG-TXD6: J41.4, JP14.2, S14.1, S14.2, U27.20, U28.K12
PA7/UART-LOG-TXD7: J47.4, JP16.2, S16.1, S16.2, U31.20, U32.K12
PA7/UART-LOG-TXD8: J53.4, JP18.2, S18.1, S18.2, U35.20, U36.K12
PA7/UART-LOG-TXD9: J59.4, JP20.2, S20.1, S20.2, U39.20, U40.K12
PA8: J12.2, U8.A12
PA8/UART-LOG-RXD: J6.5, U1.K13, U2.21
PA8/UART-LOG-RXD1: J11.5, U7.21, U8.K13
PA8/UART-LOG-RXD2: J17.5, U11.21, U12.K13
PA8/UART-LOG-RXD3: J23.5, U15.21, U16.K13
PA8/UART-LOG-RXD4: J29.5, U19.21, U20.K13
PA8/UART-LOG-RXD5: J35.5, U23.21, U24.K13
PA8/UART-LOG-RXD6: J41.5, U27.21, U28.K13
PA8/UART-LOG-RXD7: J47.5, U31.21, U32.K13
PA8/UART-LOG-RXD8: J53.5, U35.21, U36.K13
PA8/UART-LOG-RXD9: J59.5, U39.21, U40.K13
PA9: J12.3, U8.B12
PA10: J12.5, U8.A7
PA11: J18.4, U12.A9
PA12: J16.3, U12.A8
PA13: J17.3, U12.K10
PA14: J7.2, U1.A12
PA15: J7.3, U1.B12
PA16: J17.1, U12.K8
PA16/PICO: J1.17, U1.A11
PA16/PICO1: J10.17, U8.A11
PA16/PICO2: J16.17, U12.A11
PA16/PICO3: J22.17, U16.A11
PA16/PICO4: J28.17, U20.A11
PA16/PICO5: J34.17, U24.A11
PA16/PICO6: J40.17, U28.A11
PA16/PICO7: J46.17, U32.A11
PA16/PICO8: J52.17, U36.A11
PA16/PICO9: J58.17, U40.A11
PA17: J17.2, U12.K9
PA17/POCI: J1.16, U1.B11
PA17/POCI1: J10.16, U8.B11
PA17/POCI2: J16.16, U12.B11
PA17/POCI3: J22.16, U16.B11
PA17/POCI4: J28.16, U20.B11
PA17/POCI5: J34.16, U24.B11
PA17/POCI6: J40.16, U28.B11
PA17/POCI7: J46.16, U32.B11
PA17/POCI8: J52.16, U36.B11
PA17/POCI9: J58.16, U40.B11
PA18: J18.2, U12.A12
PA18/SCK: J1.18, U1.A10
PA18/SCK1: J10.18, U8.A10
PA18/SCK2: J16.18, U12.A10
PA18/SCK3: J22.18, U16.A10
PA18/SCK4: J28.18, U20.A10
PA18/SCK5: J34.18, U24.A10
PA18/SCK6: J40.18, U28.A10
PA18/SCK7: J46.18, U32.A10
PA18/SCK8: J52.18, U36.A10
PA18/SCK9: J58.18, U40.A10
PA19: J18.3, U12.B12
PA19/CS: J1.4, U1.B10
PA19/CS1: J10.4, U8.B10
PA19/CS2: J16.4, U12.B10
PA19/CS3: J22.4, U16.B10
PA19/CS4: J28.4, U20.B10
PA19/CS5: J34.4, U24.B10
PA19/CS6: J40.4, U28.B10
PA19/CS7: J46.4, U32.B10
PA19/CS8: J52.4, U36.B10
PA19/CS9: J58.4, U40.B10
PA20: J18.5, U12.A7
PA21: J24.4, U16.A9
PA22: J22.3, U16.A8
PA23: J23.3, U16.K10
PA24: J23.1, U16.K8
PA25: J23.2, U16.K9
PA25/SCL: J1.2, J3.4, U1.A5
PA25/SCL1: J8.4, J10.2, U8.A5
PA25/SCL2: J14.4, J16.2, U12.A5
PA25/SCL3: J20.4, J22.2, U16.A5
PA25/SCL4: J26.4, J28.2, U20.A5
PA25/SCL5: J32.4, J34.2, U24.A5
PA25/SCL6: J38.4, J40.2, U28.A5
PA25/SCL7: J44.4, J46.2, U32.A5
PA25/SCL8: J50.4, J52.2, U36.A5
PA25/SCL9: J56.4, J58.2, U40.A5
PA26: J24.2, U16.A12
PA26/SDA: J1.1, J3.3, U1.A6
PA26/SDA1: J8.3, J10.1, U8.A6
PA26/SDA2: J14.3, J16.1, U12.A6
PA26/SDA3: J20.3, J22.1, U16.A6
PA26/SDA4: J26.3, J28.1, U20.A6
PA26/SDA5: J32.3, J34.1, U24.A6
PA26/SDA6: J38.3, J40.1, U28.A6
PA26/SDA7: J44.3, J46.1, U32.A6
PA26/SDA8: J50.3, J52.1, U36.A6
PA26/SDA9: J56.3, J58.1, U40.A6
PA27: J7.4, U1.A9
PA28: J7.5, U1.A7
PA29: J24.3, U16.B12
PA30: J1.3, U1.A8
PA31: J24.5, U16.A7
PA32: J30.4, U20.A9
PA33: J28.3, U20.A8
PA34: J29.3, U20.K10
PA35: J29.1, U20.K8
PA36: J29.2, U20.K9
PA37: J30.2, U20.A12
PA38: J30.3, U20.B12
PA39: J30.5, U20.A7
PA40: J36.4, U24.A9
PA41: J34.3, U24.A8
PA42: J35.3, U24.K10
PA43: J35.1, U24.K8
PA44: J35.2, U24.K9
PA45: J36.2, U24.A12
PA46: J36.3, U24.B12
PA47: J36.5, U24.A7
PA48: J42.4, U28.A9
PA49: J40.3, U28.A8
PA50: J41.3, U28.K10
PA51: J41.1, U28.K8
PA52: J41.2, U28.K9
PA53: J42.2, U28.A12
PA54: J42.3, U28.B12
PA55: J42.5, U28.A7
PA56: J48.4, U32.A9
PA57: J46.3, U32.A8
PA58: J47.3, U32.K10
PA59: J47.1, U32.K8
PA60: J47.2, U32.K9
PA61: J48.2, U32.A12
PA62: J48.3, U32.B12
PA63: J48.5, U32.A7
PA64: J54.4, U36.A9
PA65: J52.3, U36.A8
PA66: J53.3, U36.K10
PA67: J53.1, U36.K8
PA68: J53.2, U36.K9
PA69: J54.2, U36.A12
PA70: J54.3, U36.B12
PA71: J54.5, U36.A7
PA72: J60.4, U40.A9
PA73: J58.3, U40.A8
PA74: J59.3, U40.K10
PA75: J59.1, U40.K8
PA76: J59.2, U40.K9
PA77: J60.2, U40.A12
PA78: J60.3, U40.B12
PA79: J60.5, U40.A7
PB1: J10.7, U8.K1
PB1/A1: J10.20, U8.A3
PB1/A2: J16.20, U12.A3
PB1/A3: J22.20, U16.A3
PB1/A4: J1.20, U1.A3
PB1/A5: J28.20, U20.A3
PB1/A6: J34.20, U24.A3
PB1/A7: J40.20, U28.A3
PB1/A8: J46.20, U32.A3
PB1/A9: J52.20, U36.A3
PB1/A10: J58.20, U40.A3
PB2: J10.6, U8.K2
PB2/A1: J10.19, U8.A4
PB2/A2: J16.19, U12.A4
PB2/A3: J22.19, U16.A4
PB2/A4: J28.19, U20.A4
PB2/A5: J1.19, U1.A4
PB2/A6: J34.19, U24.A4
PB2/A7: J40.19, U28.A4
PB2/A8: J46.19, U32.A4
PB2/A9: J52.19, U36.A4
PB2/A10: J58.19, U40.A4
PB3: J10.8, U8.K5
PB3/A1: J10.5, U8.B1
PB3/A2: J16.5, U12.B1
PB3/A3: J22.5, U16.B1
PB3/A4: J28.5, U20.B1
PB3/A5: J34.5, U24.B1
PB3/A6: J1.5, U1.B1
PB3/A7: J40.5, U28.B1
PB3/A8: J46.5, U32.B1
PB3/A9: J52.5, U36.B1
PB3/A10: J58.5, U40.B1
PB4: J10.9, R21.1, U8.K6
PB4/A0: J1.24, U1.B2
PB4/A1: J10.24, U8.B2
PB4/A2: J16.24, U12.B2
PB4/A3: J22.24, U16.B2
PB4/A4: J28.24, U20.B2
PB4/A5: J34.24, U24.B2
PB4/A6: J40.24, U28.B2
PB4/A7: J46.24, U32.B2
PB4/A8: J52.24, U36.B2
PB4/A9: J58.24, U40.B2
PB5: J10.13, U8.K7
PB5/A1: J1.23, U1.C1
PB5/A2: J10.23, U8.C1
PB5/A3: J16.23, U12.C1
PB5/A4: J22.23, U16.C1
PB5/A5: J28.23, U20.C1
PB5/A6: J34.23, U24.C1
PB5/A7: J40.23, U28.C1
PB5/A8: J46.23, U32.C1
PB5/A9: J52.23, U36.C1
PB5/A10: J58.23, U40.C1
PB6: J16.7, U12.K1
PB6/A1: J10.22, U8.C2
PB6/A2: J1.22, U1.C2
PB6/A3: J16.22, U12.C2
PB6/A4: J22.22, U16.C2
PB6/A5: J28.22, U20.C2
PB6/A6: J34.22, U24.C2
PB6/A7: J40.22, U28.C2
PB6/A8: J46.22, U32.C2
PB6/A9: J52.22, U36.C2
PB6/A10: J58.22, U40.C2
PB7: J16.6, U12.K2
PB7/A1: J10.21, U8.D1
PB7/A2: J16.21, U12.D1
PB7/A3: J1.21, U1.D1
PB7/A4: J22.21, U16.D1
PB7/A5: J28.21, U20.D1
PB7/A6: J34.21, U24.D1
PB7/A7: J40.21, U28.D1
PB7/A8: J46.21, U32.D1
PB7/A9: J52.21, U36.D1
PB7/A10: J58.21, U40.D1
PB8: J16.8, U12.K5
PB9: J16.9, R37.1, U12.K6
PB10: J16.13, U12.K7
PB11: J22.7, U16.K1
PB12: J22.6, U16.K2
PB13: J22.8, U16.K5
PB14: J22.9, R53.1, U16.K6
PB15: J22.13, U16.K7
PB16: J28.7, U20.K1
PB17: J28.6, U20.K2
PB18: J28.8, U20.K5
PB19: J28.9, R69.1, U20.K6
PB20: J28.13, U20.K7
PB21: J34.7, U24.K1
PB22: J1.7, U1.K1
PB23: J1.6, U1.K2
PB24: J34.6, U24.K2
PB25: J34.8, U24.K5
PB26: J1.8, U1.K5
PB27: J34.9, R85.1, U24.K6
PB28: J34.13, U24.K7
PB29: J1.9, R4.1, U1.K6
PB30: J40.7, U28.K1
PB31: J1.13, U1.K7
PB32: J40.6, U28.K2
PB33: J40.8, U28.K5
PB34: J40.9, R101.1, U28.K6
PB35: J40.13, U28.K7
PB36: J46.7, U32.K1
PB37: J46.6, U32.K2
PB38: J46.8, U32.K5
PB39: J46.9, R117.1, U32.K6
PB40: J46.13, U32.K7
PB41: J52.7, U36.K1
PB42: J52.6, U36.K2
PB43: J52.8, U36.K5
PB44: J52.9, R133.1, U36.K6
PB45: J52.13, U36.K7
PB46: J58.7, U40.K1
PB47: J58.6, U40.K2
PB48: J58.8, U40.K5
PB49: J58.9, R149.1, U40.K6
PB50: J58.13, U40.K7
RTS: Q2.4, R18.1, U2.19
RTS1: Q4.4, R31.1, U7.19
RTS2: Q6.4, R47.1, U11.19
RTS3: Q8.4, R63.1, U15.19
RTS4: Q10.4, R79.1, U19.19
RTS5: Q12.4, R95.1, U23.19
RTS6: Q14.4, R111.1, U27.19
RTS7: Q16.4, R127.1, U31.19
RTS8: Q18.4, R143.1, U35.19
RTS9: Q20.4, R159.1, U39.19
USB_SHLD: J5.SHLD1, J5.SHLD2, J5.SHLD3, J5.SHLD4, J5.SHLD5, J5.SHLD6, J5.SHLD7, J5.SHLD8, USBSHLD.2
USB_SHLD1: J9.SHLD1, J9.SHLD2, J9.SHLD3, J9.SHLD4, J9.SHLD5, J9.SHLD6, J9.SHLD7, J9.SHLD8, USBSHLD1.2
USB_SHLD2: J15.SHLD1, J15.SHLD2, J15.SHLD3, J15.SHLD4, J15.SHLD5, J15.SHLD6, J15.SHLD7, J15.SHLD8, USBSHLD2.2
USB_SHLD3: J21.SHLD1, J21.SHLD2, J21.SHLD3, J21.SHLD4, J21.SHLD5, J21.SHLD6, J21.SHLD7, J21.SHLD8, USBSHLD3.2
USB_SHLD4: J27.SHLD1, J27.SHLD2, J27.SHLD3, J27.SHLD4, J27.SHLD5, J27.SHLD6, J27.SHLD7, J27.SHLD8, USBSHLD4.2
USB_SHLD5: J33.SHLD1, J33.SHLD2, J33.SHLD3, J33.SHLD4, J33.SHLD5, J33.SHLD6, J33.SHLD7, J33.SHLD8, USBSHLD5.2
USB_SHLD6: J39.SHLD1, J39.SHLD2, J39.SHLD3, J39.SHLD4, J39.SHLD5, J39.SHLD6, J39.SHLD7, J39.SHLD8, USBSHLD6.2
USB_SHLD7: J45.SHLD1, J45.SHLD2, J45.SHLD3, J45.SHLD4, J45.SHLD5, J45.SHLD6, J45.SHLD7, J45.SHLD8, USBSHLD7.2
USB_SHLD8: J51.SHLD1, J51.SHLD2, J51.SHLD3, J51.SHLD4, J51.SHLD5, J51.SHLD6, J51.SHLD7, J51.SHLD8, USBSHLD8.2
USB_SHLD9: J57.SHLD1, J57.SHLD2, J57.SHLD3, J57.SHLD4, J57.SHLD5, J57.SHLD6, J57.SHLD7, J57.SHLD8, USBSHLD9.2
VIN: C7.1, D2.C, Q1.2, R8.1, U3.1
VIN1: C5.1, D5.C, Q3.2, R22.1, U6.1
VIN2: C16.1, D11.C, Q5.2, R38.1, U10.1
VIN3: C25.1, D16.C, Q7.2, R54.1, U14.1
VIN4: C33.1, D21.C, Q9.2, R70.1, U18.1
VIN5: C41.1, D26.C, Q11.2, R86.1, U22.1
VIN6: C49.1, D31.C, Q13.2, R102.1, U26.1
VIN7: C57.1, D36.C, Q15.2, R118.1, U30.1
VIN8: C65.1, D41.C, Q17.2, R134.1, U34.1
VIN9: C73.1, D46.C, Q19.2, R150.1, U38.1
V_BATT: C6.1, J1.12, J2.2, Q1.3, U1.D2, U4.3
V_BATT1: C9.1, J4.2, J10.12, Q3.3, U5.3, U8.D2
V_BATT2: C18.1, J13.2, J16.12, Q5.3, U9.3, U12.D2
V_BATT3: C27.1, J19.2, J22.12, Q7.3, U13.3, U16.D2
V_BATT4: C35.1, J25.2, J28.12, Q9.3, U17.3, U20.D2
V_BATT5: C43.1, J31.2, J34.12, Q11.3, U21.3, U24.D2
V_BATT6: C51.1, J37.2, J40.12, Q13.3, U25.3, U28.D2
V_BATT7: C59.1, J43.2, J46.12, Q15.3, U29.3, U32.D2
V_BATT8: C67.1, J49.2, J52.12, Q17.3, U33.3, U36.D2
V_BATT9: C75.1, J55.2, J58.12, Q19.3, U37.3, U40.D2
V_USB: C19.1, D2.A, D6.5, J1.10, J5.VBUS1, J5.VBUS2, R3.1, R5.2, R7.2, R10.1, U4.4
V_USB1: C11.1, D5.A, D10.5, J9.VBUS1, J9.VBUS2, J10.10, R14.2, R16.1, R23.2, R28.1, U5.4
V_USB2: C20.1, D11.A, D15.5, J15.VBUS1, J15.VBUS2, J16.10, R33.2, R34.1, R39.2, R44.1, U9.4
V_USB3: C28.1, D16.A, D20.5, J21.VBUS1, J21.VBUS2, J22.10, R49.2, R50.1, R55.2, R60.1, U13.4
V_USB4: C36.1, D21.A, D25.5, J27.VBUS1, J27.VBUS2, J28.10, R65.2, R66.1, R71.2, R76.1, U17.4
V_USB5: C44.1, D26.A, D30.5, J33.VBUS1, J33.VBUS2, J34.10, R81.2, R82.1, R87.2, R92.1, U21.4
V_USB6: C52.1, D31.A, D35.5, J39.VBUS1, J39.VBUS2, J40.10, R97.2, R98.1, R103.2, R108.1, U25.4
V_USB7: C60.1, D36.A, D40.5, J45.VBUS1, J45.VBUS2, J46.10, R113.2, R114.1, R119.2, R124.1, U29.4
V_USB8: C68.1, D41.A, D45.5, J51.VBUS1, J51.VBUS2, J52.10, R129.2, R130.1, R135.2, R140.1, U33.4
V_USB9: C76.1, D46.A, D50.5, J57.VBUS1, J57.VBUS2, J58.10, R145.2, R146.1, R151.2, R156.1, U37.4
